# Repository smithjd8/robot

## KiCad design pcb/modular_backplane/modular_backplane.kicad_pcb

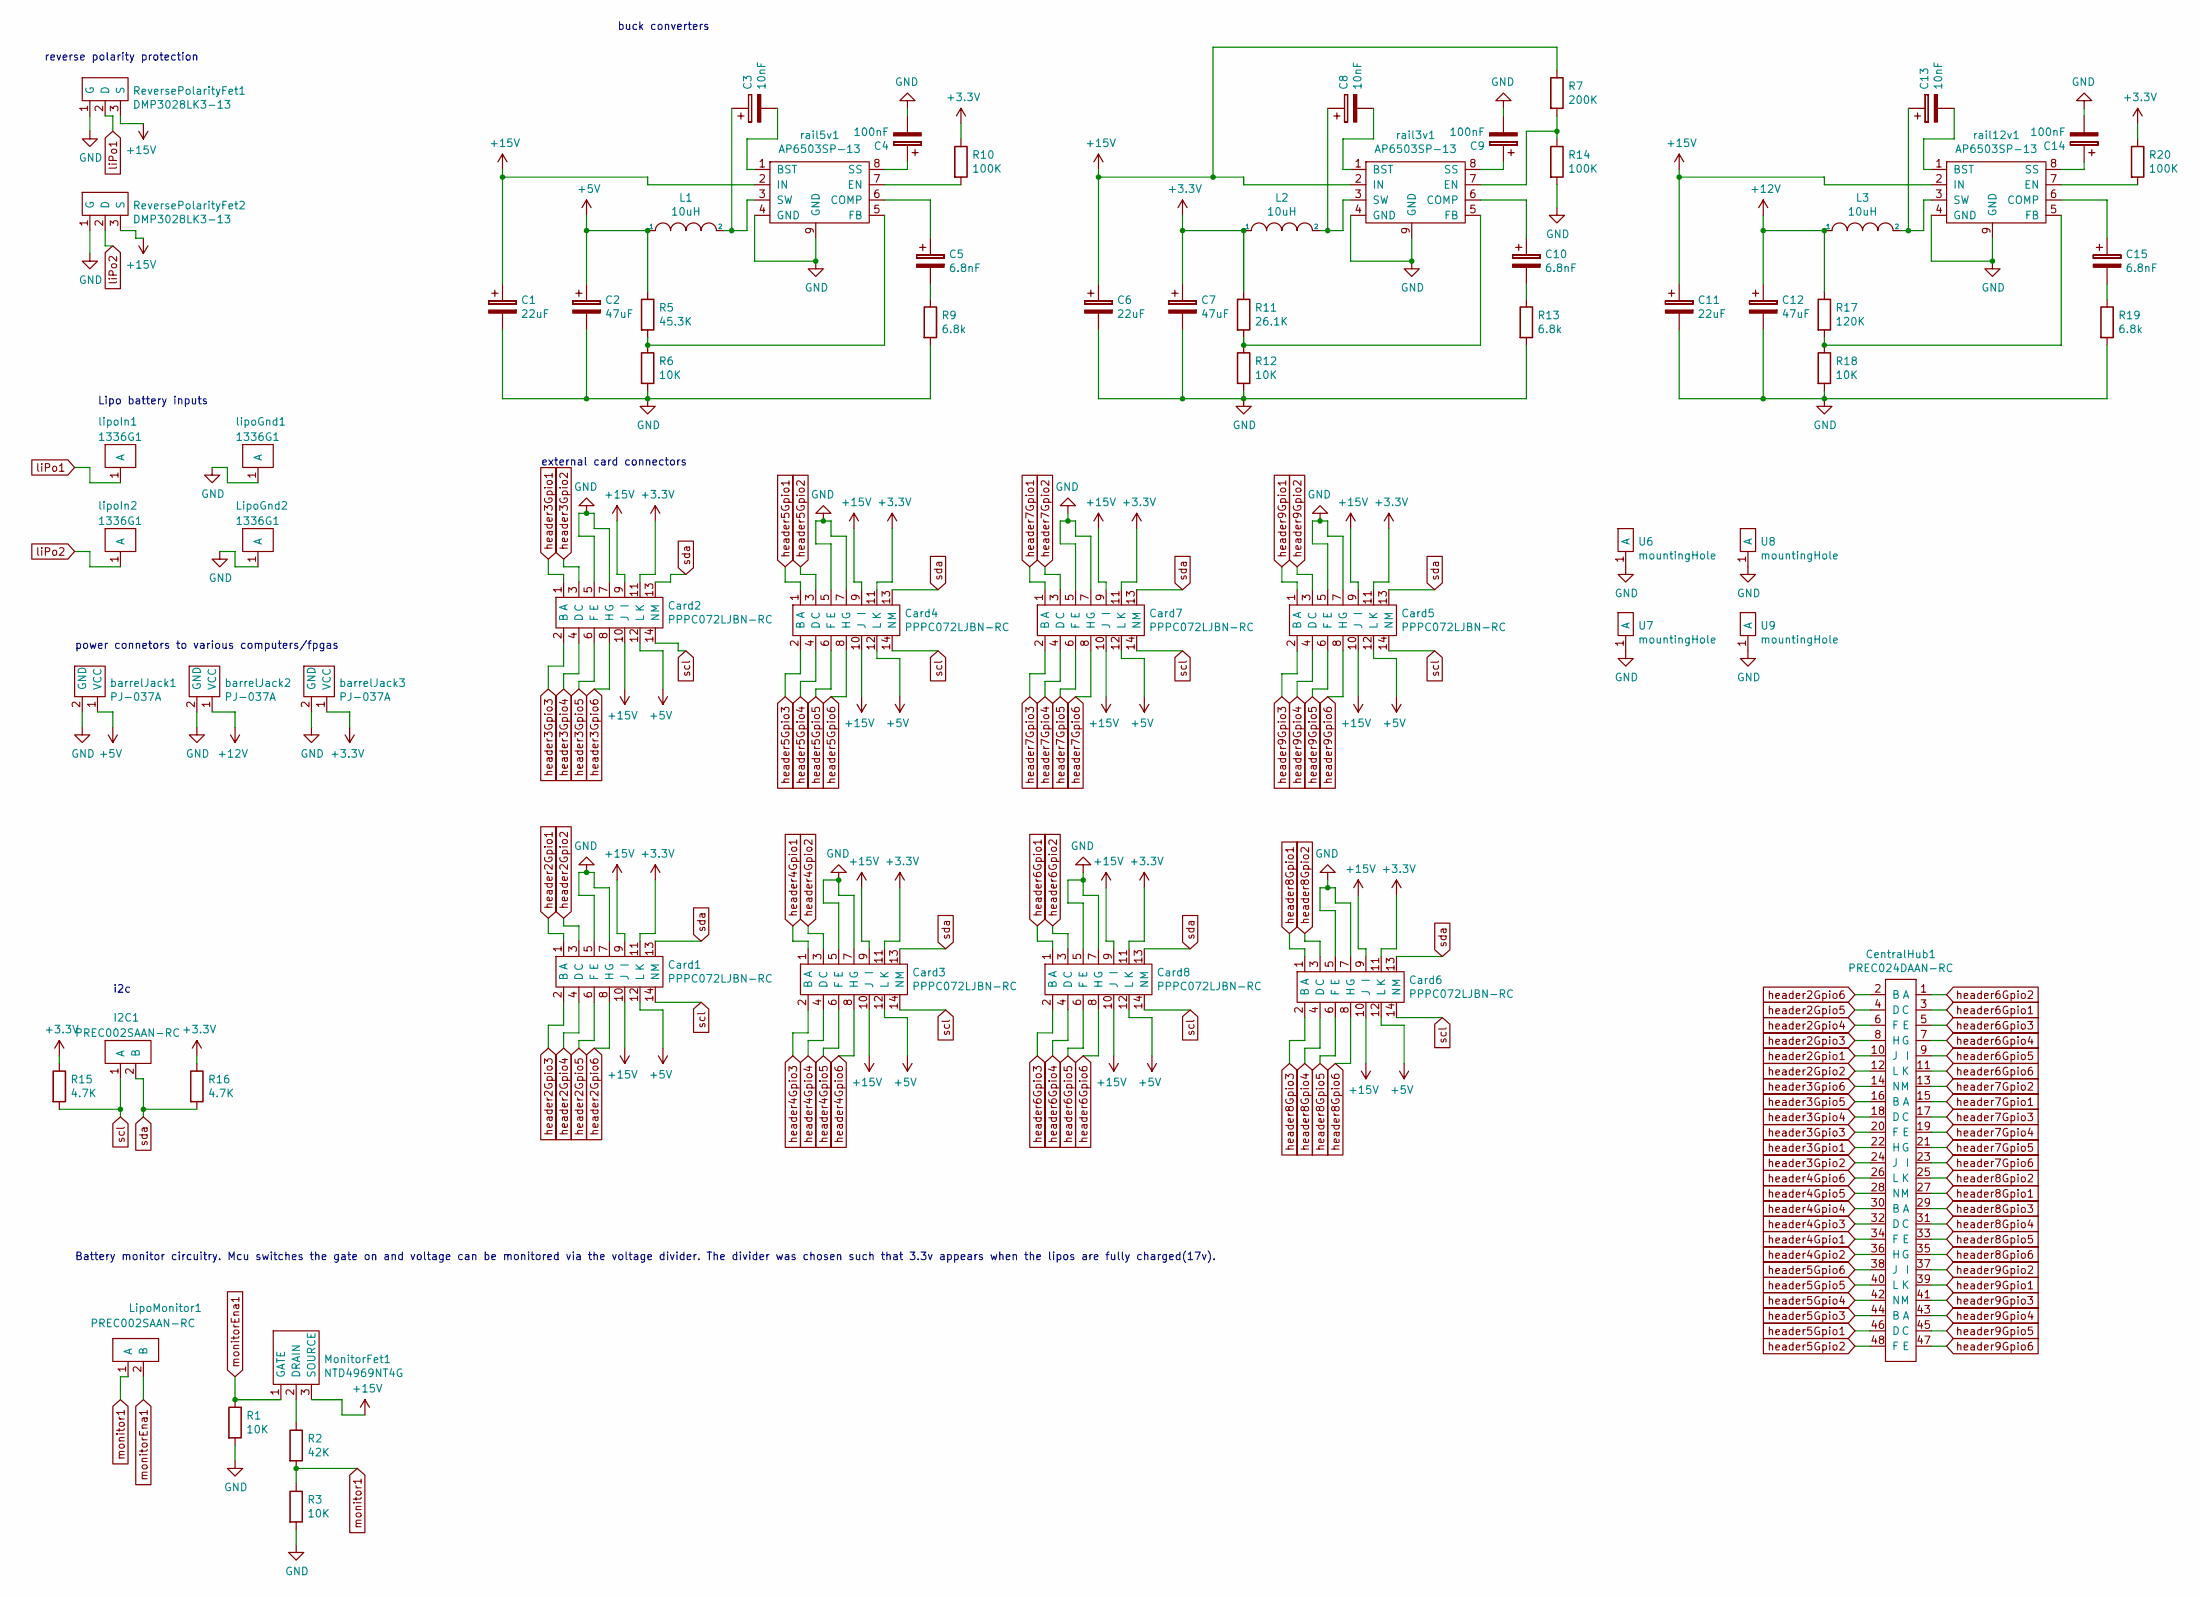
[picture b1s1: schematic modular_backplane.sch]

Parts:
C1, C6, C11: 22uF; 865090442004
C2, C7, C12: 47uF; 865090449007
C3, C8, C13: 10nF; C_1206_3216Metric_Pad1.42x1.75mm_HandSolder
C4, C9, C14: 100nF; C_1206_3216Metric_Pad1.42x1.75mm_HandSolder
C5, C10, C15: 6.8nF; C_1206_3216Metric_Pad1.42x1.75mm_HandSolder
Card1, Card2, Card3, Card4, Card5, Card6, Card7, Card8: PPPC072LJBN-RC
CentralHub1: PREC024DAAN-RC
I2C1: PREC002SAAN-RC
L1, L2, L3: 10uH; RCH8011NP-100L
LipoGnd2: 1336G1
LipoMonitor1: PREC002SAAN-RC
MonitorFet1: NTD4969NT4G
R1, R3, R6, R12, R18: 10K; R_1206_3216Metric_Pad1.42x1.75mm_HandSolder
R2: 42K; R_1206_3216Metric_Pad1.42x1.75mm_HandSolder
R5: 45.3K; R_1206_3216Metric_Pad1.42x1.75mm_HandSolder
R7: 200K; R_1206_3216Metric_Pad1.42x1.75mm_HandSolder
R9, R13, R19: 6.8k; R_1206_3216Metric_Pad1.42x1.75mm_HandSolder
R10, R14, R20: 100K; R_1206_3216Metric_Pad1.42x1.75mm_HandSolder
R11: 26.1K; R_1206_3216Metric_Pad1.42x1.75mm_HandSolder
R15, R16: 4.7K; R_1206_3216Metric_Pad1.42x1.75mm_HandSolder
R17: 120K; R_1206_3216Metric_Pad1.42x1.75mm_HandSolder
ReversePolarityFet1, ReversePolarityFet2: DMP3028LK3-13
U6, U7, U8, U9: mountingHole
barrelJack1, barrelJack2, barrelJack3: PJ-037A
lipoGnd1: 1336G1
lipoIn1, lipoIn2: 1336G1
rail3v1, rail5v1, rail12v1: AP6503SP-13

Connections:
+3V3: C7.1, Card1.11 (K), Card2.11 (K), Card3.11 (K), Card4.11 (K), Card5.11 (K), Card6.11 (K), Card7.11 (K), Card8.11 (K), L2.1, R10.1, R11.1, R15.1, R16.1, R20.1, barrelJack3.1 (VCC)
+5V: C2.1, Card1.12 (L), Card2.12 (L), Card3.12 (L), Card4.12 (L), Card5.12 (L), Card6.12 (L), Card7.12 (L), Card8.12 (L), L1.1, R5.1, barrelJack1.1 (VCC)
+12V: C12.1, L3.1, R17.1, barrelJack2.1 (VCC)
+15V: C1.1, C6.1, C11.1, Card1.9 (I), Card1.10 (J), Card2.9 (I), Card2.10 (J), Card3.9 (I), Card3.10 (J), Card4.9 (I), Card4.10 (J), Card5.9 (I), Card5.10 (J), Card6.9 (I), Card6.10 (J), Card7.9 (I), Card7.10 (J), Card8.9 (I), Card8.10 (J), MonitorFet1.3 (SOURCE), R7.1, ReversePolarityFet1.3 (S), ReversePolarityFet2.3 (S), rail3v1.2 (IN), rail5v1.2 (IN), rail12v1.2 (IN)
GND: C1.2, C2.2, C4.2, C6.2, C7.2, C9.2, C11.2, C12.2, C14.2, Card1.5 (E), Card1.7 (G), Card2.5 (E), Card2.7 (G), Card3.5 (E), Card3.7 (G), Card4.5 (E), Card4.7 (G), Card5.5 (E), Card5.7 (G), Card6.5 (E), Card6.7 (G), Card7.5 (E), Card7.7 (G), Card8.5 (E), Card8.7 (G), LipoGnd2.1, R1.2, R3.2, R6.2, R9.2, R12.2, R13.2, R14.2, R18.2, R19.2, ReversePolarityFet1.1 (G), ReversePolarityFet2.1 (G), U6.1, U7.1, U8.1, U9.1, barrelJack1.2 (GND), barrelJack2.2 (GND), barrelJack3.2 (GND), lipoGnd1.1, rail3v1.4 (GND), rail3v1.9 (GND), rail5v1.4 (GND), rail5v1.9 (GND), rail12v1.4 (GND), rail12v1.9 (GND)
unnamed: C3.1, L1.2, rail5v1.3 (SW)
unnamed: C3.2, rail5v1.1 (BST)
unnamed: C4.1, rail5v1.8 (SS)
unnamed: C5.1, rail5v1.6 (COMP)
unnamed: C5.2, R9.1
unnamed: C8.1, L2.2, rail3v1.3 (SW)
unnamed: C8.2, rail3v1.1 (BST)
unnamed: C9.1, rail3v1.8 (SS)
unnamed: C10.1, rail3v1.6 (COMP)
unnamed: C10.2, R13.1
unnamed: C13.1, L3.2, rail12v1.3 (SW)
unnamed: C13.2, rail12v1.1 (BST)
unnamed: C14.1, rail12v1.8 (SS)
unnamed: C15.1, rail12v1.6 (COMP)
unnamed: C15.2, R19.1
unnamed: MonitorFet1.2 (DRAIN), R2.1
unnamed: R5.2, R6.1, rail5v1.5 (FB)
unnamed: R10.2, rail5v1.7 (EN)
unnamed: R11.2, R12.1, rail3v1.5 (FB)
unnamed: R7.2, R14.1, rail3v1.7 (EN)
unnamed: R17.2, R18.1, rail12v1.5 (FB)
unnamed: R20.2, rail12v1.7 (EN)
header2Gpio1: Card1.1 (A), CentralHub1.10 (J)
header2Gpio2: Card1.3 (C), CentralHub1.12 (L)
header2Gpio3: Card1.2 (B), CentralHub1.8 (H)
header2Gpio4: Card1.4 (D), CentralHub1.6 (F)
header2Gpio5: Card1.6 (F), CentralHub1.4 (D)
header2Gpio6: Card1.8 (H), CentralHub1.2 (B)
header3Gpio1: Card2.1 (A), CentralHub1.22 (H)
header3Gpio2: Card2.3 (C), CentralHub1.24 (J)
header3Gpio3: Card2.2 (B), CentralHub1.20 (F)
header3Gpio4: Card2.4 (D), CentralHub1.18 (D)
header3Gpio5: Card2.6 (F), CentralHub1.16 (B)
header3Gpio6: Card2.8 (H), CentralHub1.14 (N)
header4Gpio1: Card3.1 (A), CentralHub1.34 (F)
header4Gpio2: Card3.3 (C), CentralHub1.36 (H)
header4Gpio3: Card3.2 (B), CentralHub1.32 (D)
header4Gpio4: Card3.4 (D), CentralHub1.30 (B)
header4Gpio5: Card3.6 (F), CentralHub1.28 (N)
header4Gpio6: Card3.8 (H), CentralHub1.26 (L)
header5Gpio1: Card4.1 (A), CentralHub1.46 (D)
header5Gpio2: Card4.3 (C), CentralHub1.48 (F)
header5Gpio3: Card4.2 (B), CentralHub1.44 (B)
header5Gpio4: Card4.4 (D), CentralHub1.42 (N)
header5Gpio5: Card4.6 (F), CentralHub1.40 (L)
header5Gpio6: Card4.8 (H), CentralHub1.38 (J)
header6Gpio1: Card8.1 (A), CentralHub1.3 (C)
header6Gpio2: Card8.3 (C), CentralHub1.1 (A)
header6Gpio3: Card8.2 (B), CentralHub1.5 (E)
header6Gpio4: Card8.4 (D), CentralHub1.7 (G)
header6Gpio5: Card8.6 (F), CentralHub1.9 (I)
header6Gpio6: Card8.8 (H), CentralHub1.11 (K)
header7Gpio1: Card7.1 (A), CentralHub1.15 (A)
header7Gpio2: Card7.3 (C), CentralHub1.13 (M)
header7Gpio3: Card7.2 (B), CentralHub1.17 (C)
header7Gpio4: Card7.4 (D), CentralHub1.19 (E)
header7Gpio5: Card7.6 (F), CentralHub1.21 (G)
header7Gpio6: Card7.8 (H), CentralHub1.23 (I)
header8Gpio1: Card6.1 (A), CentralHub1.27 (M)
header8Gpio2: Card6.3 (C), CentralHub1.25 (K)
header8Gpio3: Card6.2 (B), CentralHub1.29 (A)
header8Gpio4: Card6.4 (D), CentralHub1.31 (C)
header8Gpio5: Card6.6 (F), CentralHub1.33 (E)
header8Gpio6: Card6.8 (H), CentralHub1.35 (G)
header9Gpio1: Card5.1 (A), CentralHub1.39 (K)
header9Gpio2: Card5.3 (C), CentralHub1.37 (I)
header9Gpio3: Card5.2 (B), CentralHub1.41 (M)
header9Gpio4: Card5.4 (D), CentralHub1.43 (A)
header9Gpio5: Card5.6 (F), CentralHub1.45 (C)
header9Gpio6: Card5.8 (H), CentralHub1.47 (E)
liPo1: ReversePolarityFet1.2 (D), lipoIn1.1
liPo2: ReversePolarityFet2.2 (D), lipoIn2.1
monitor1: LipoMonitor1.1 (A), R2.2, R3.1
monitorEna1: LipoMonitor1.2 (B), MonitorFet1.1 (GATE), R1.1
scl: Card1.14 (N), Card2.14 (N), Card3.14 (N), Card4.14 (N), Card5.14 (N), Card6.14 (N), Card7.14 (N), Card8.14 (N), I2C1.1 (A), R15.2
sda: Card1.13 (M), Card2.13 (M), Card3.13 (M), Card4.13 (M), Card5.13 (M), Card6.13 (M), Card7.13 (M), Card8.13 (M), I2C1.2 (B), R16.2

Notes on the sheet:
reverse polarity protection
Lipo battery inputs
power connetors to various computers/fpgas
buck converters
Battery monitor circuitry. Mcu switches the gate on and voltage can be monitored via the voltage divider. The divider was chosen such that 3.3v appears when the lipos are fully charged(17v).
i2c
external card connectors

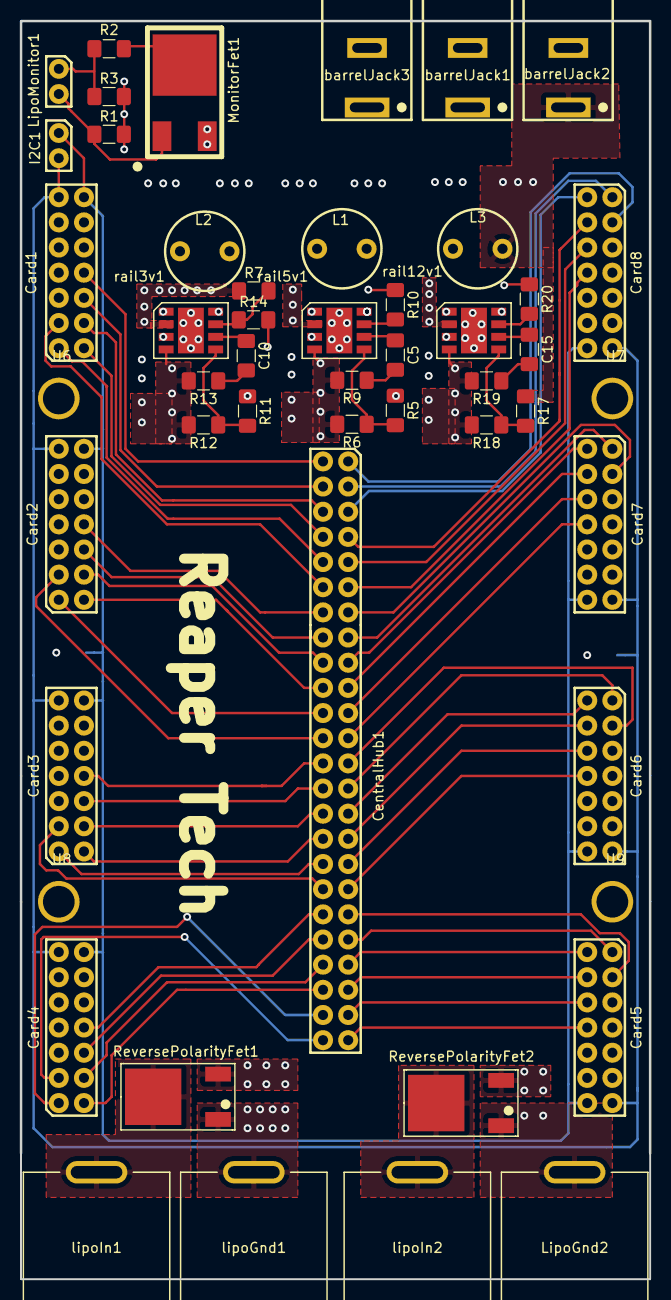
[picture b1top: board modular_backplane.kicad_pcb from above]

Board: 6 copper layers, 63.5 x 127.0 mm, 64 parts (0 on the bottom side), 81 nets.

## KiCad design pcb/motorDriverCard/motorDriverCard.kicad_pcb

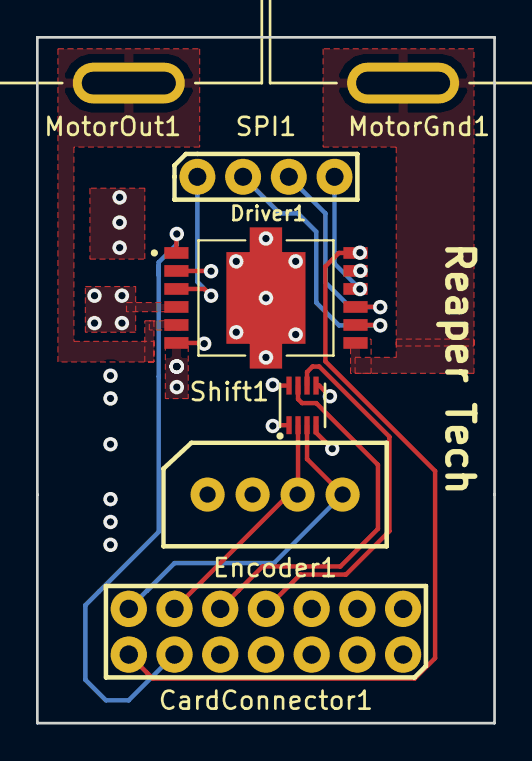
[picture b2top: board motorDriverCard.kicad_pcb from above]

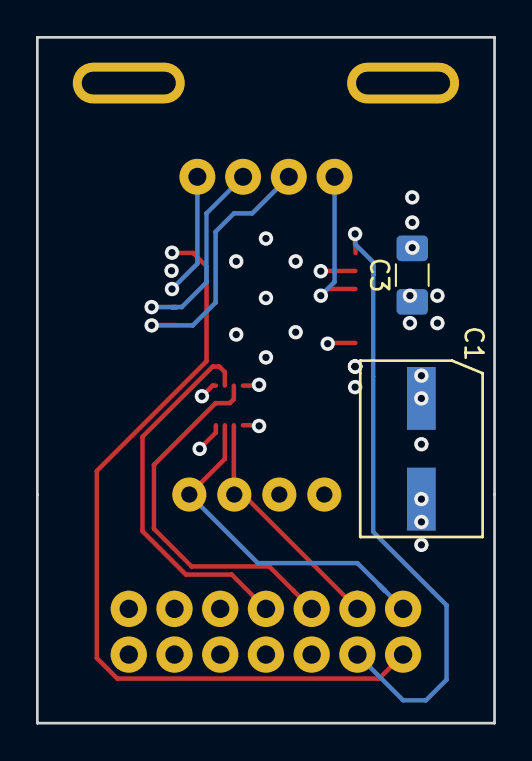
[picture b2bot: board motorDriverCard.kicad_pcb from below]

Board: 6 copper layers, 25.4 x 38.1 mm, 9 parts (2 on the bottom side), 16 nets.

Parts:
C1: 100uF; 865080445010
C3: 100nF; C_1206_3216Metric_Pad1.42x1.75mm_HandSolder
CardConnector1: PEC07DBBN
Driver1: IFX9201SGAUMA1
Encoder1: B4B-XH-A
MotorGnd1: 1336G1
MotorOut1: 1336G1
SPI1: PREC004SAAN-RC
Shift1: 74LVCH2T45DC,125

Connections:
+3V3: CardConnector1.3, Driver1.2, Shift1.5, Shift1.8
+5V: CardConnector1.4, Encoder1.1, Shift1.1
+15V: C1.1, C3.1, CardConnector1.5, CardConnector1.6, Driver1.4
CSN: Driver1.9, SPI1.3
GND: C1.2, C3.2, CardConnector1.7, CardConnector1.9, Driver1.6, Driver1.11, Driver1.13, Encoder1.2, Shift1.4
Motor1EncoderA: CardConnector1.12, Encoder1.3, Shift1.2
Motor1EncoderA_3v3: CardConnector1.10, Shift1.7
Motor1EncoderB: CardConnector1.14, Encoder1.4, Shift1.3
Motor1EncoderB_3v3: CardConnector1.8, Shift1.6
SCK: Driver1.10, SPI1.4
mcuSI: Driver1.8, SPI1.2
mcuSO: Driver1.3, SPI1.1
motorControlOut1: Driver1.5, MotorOut1.1
motorDir1: CardConnector1.11, Driver1.1
motorGnd1: Driver1.7, MotorGnd1.1
motorPwm1: CardConnector1.13, Driver1.12

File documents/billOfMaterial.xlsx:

name | part number | quantity | price | part cost | total cost
powerpole contact | 1336g1 | 12 | 0.62 | 7.4399999999999995
powerpole housing | 1327G6FP-BK | 12 | 0.36 | 4.32
jst | B4B-XH-A | 8 | 0.21 | 1.68
male pin | PREC002SAAN-RC | 12 | 0.06 | 0.72
barrel jack | PJ-037A | 3 | 0.57999999999999996 | 1.7399999999999998
level shifter | 74LVCH2T45DC,125 | 4 | 0.155 | 0.62
PREC004SAAN-RC | male pin | 1 | 0.34 | 0.34
male pin | PREC004SAAN-RC | 5 | 0.12 | 0.6
motor driver | IFX9201SGAUMA1 | 4 | 3.84 | 15.36
regulator | AP6503SP-13 | 3 | 0.94 | 2.82
10K rsistor 1206 | RCG120610K0FKEA | 5 | 0.1 | 0.5
42k resistor 1206 | CRCW120642K2FKEA | 2 | 0.13 | 0.26
6.8k resistor 1206 | CRCW12066K80FKEAC | 3 | 0.19 | 0.57000000000000006
100k resistor 1206 | CRCW1206100KFKEAC | 3 | 0.1 | 0.30000000000000004
p channel mosfet | DMP3028LK3-13 | 2 | 0.56000000000000005 | 1.1200000000000001
inductor 15uH | 6100-150K-RC | 3 | 0.79 | 2.37
10nF | VJ1206Y103JXXPW1BC | 3 | 0.2 | 0.60000000000000009
6.8nF | VJ1206Y682KXXCW1BC | 3 | 0.1 | 0.30000000000000004
47uF | 865090449007 | 3 | 0.48 | 1.44
22uF | 865090442004 | 3 | 0.28000000000000003 | 0.84000000000000008
100nF cap | VJ1206Y104KXXPW1BC | 4 | 0.28999999999999998 | 1.1599999999999999
100uF cap | 865080445010 | 3 | 0.34 | 1.02 | 46.11999999999999

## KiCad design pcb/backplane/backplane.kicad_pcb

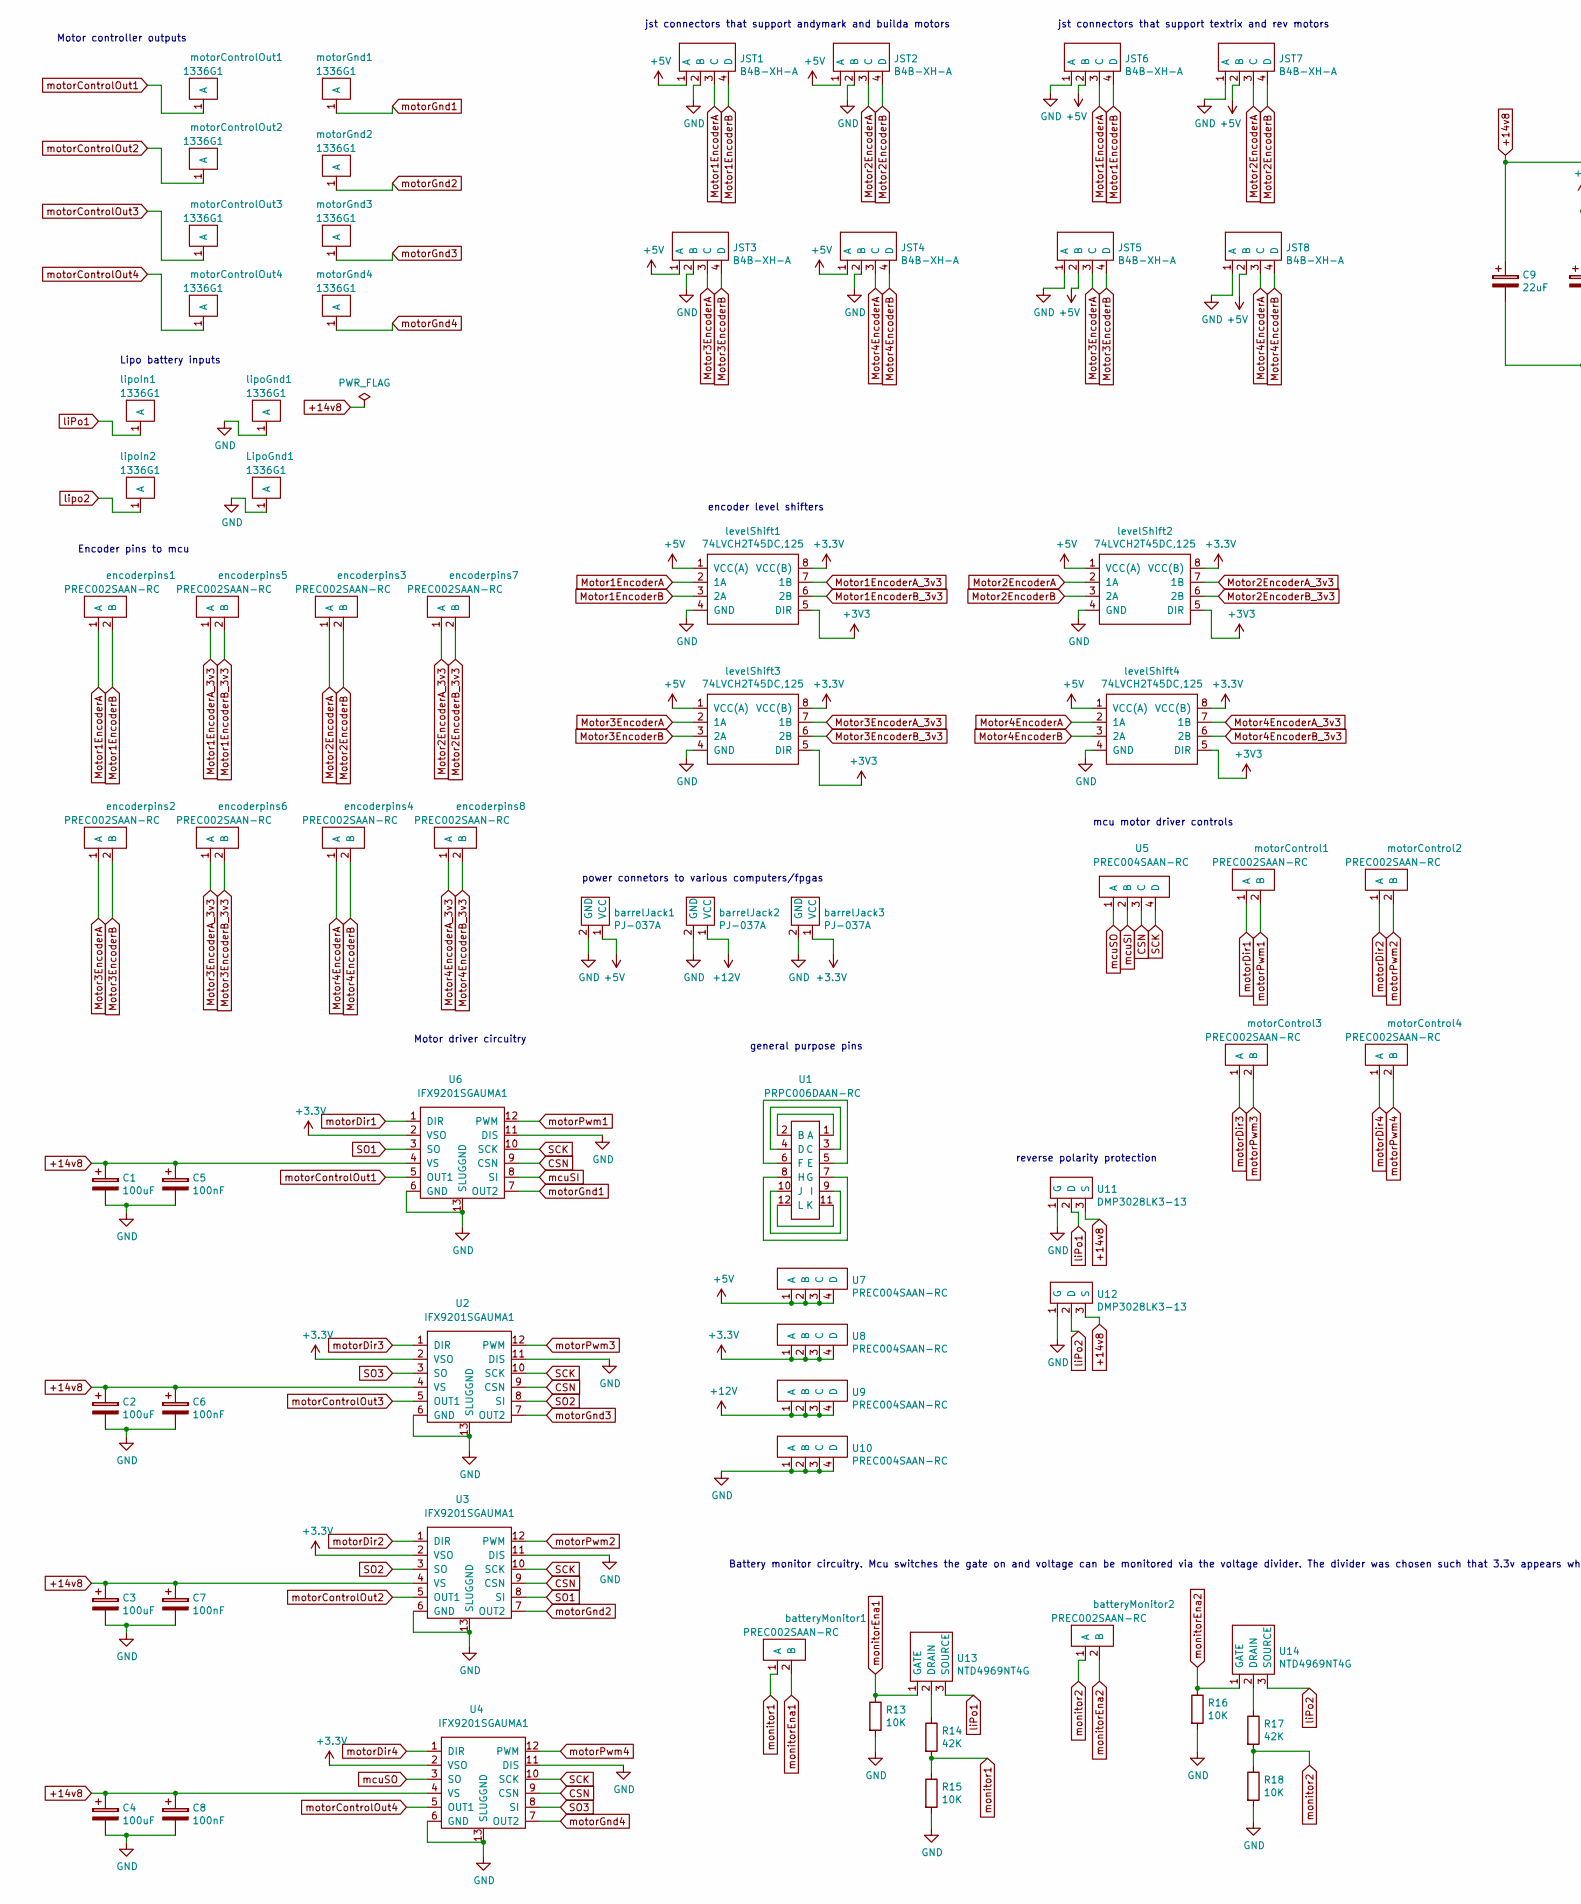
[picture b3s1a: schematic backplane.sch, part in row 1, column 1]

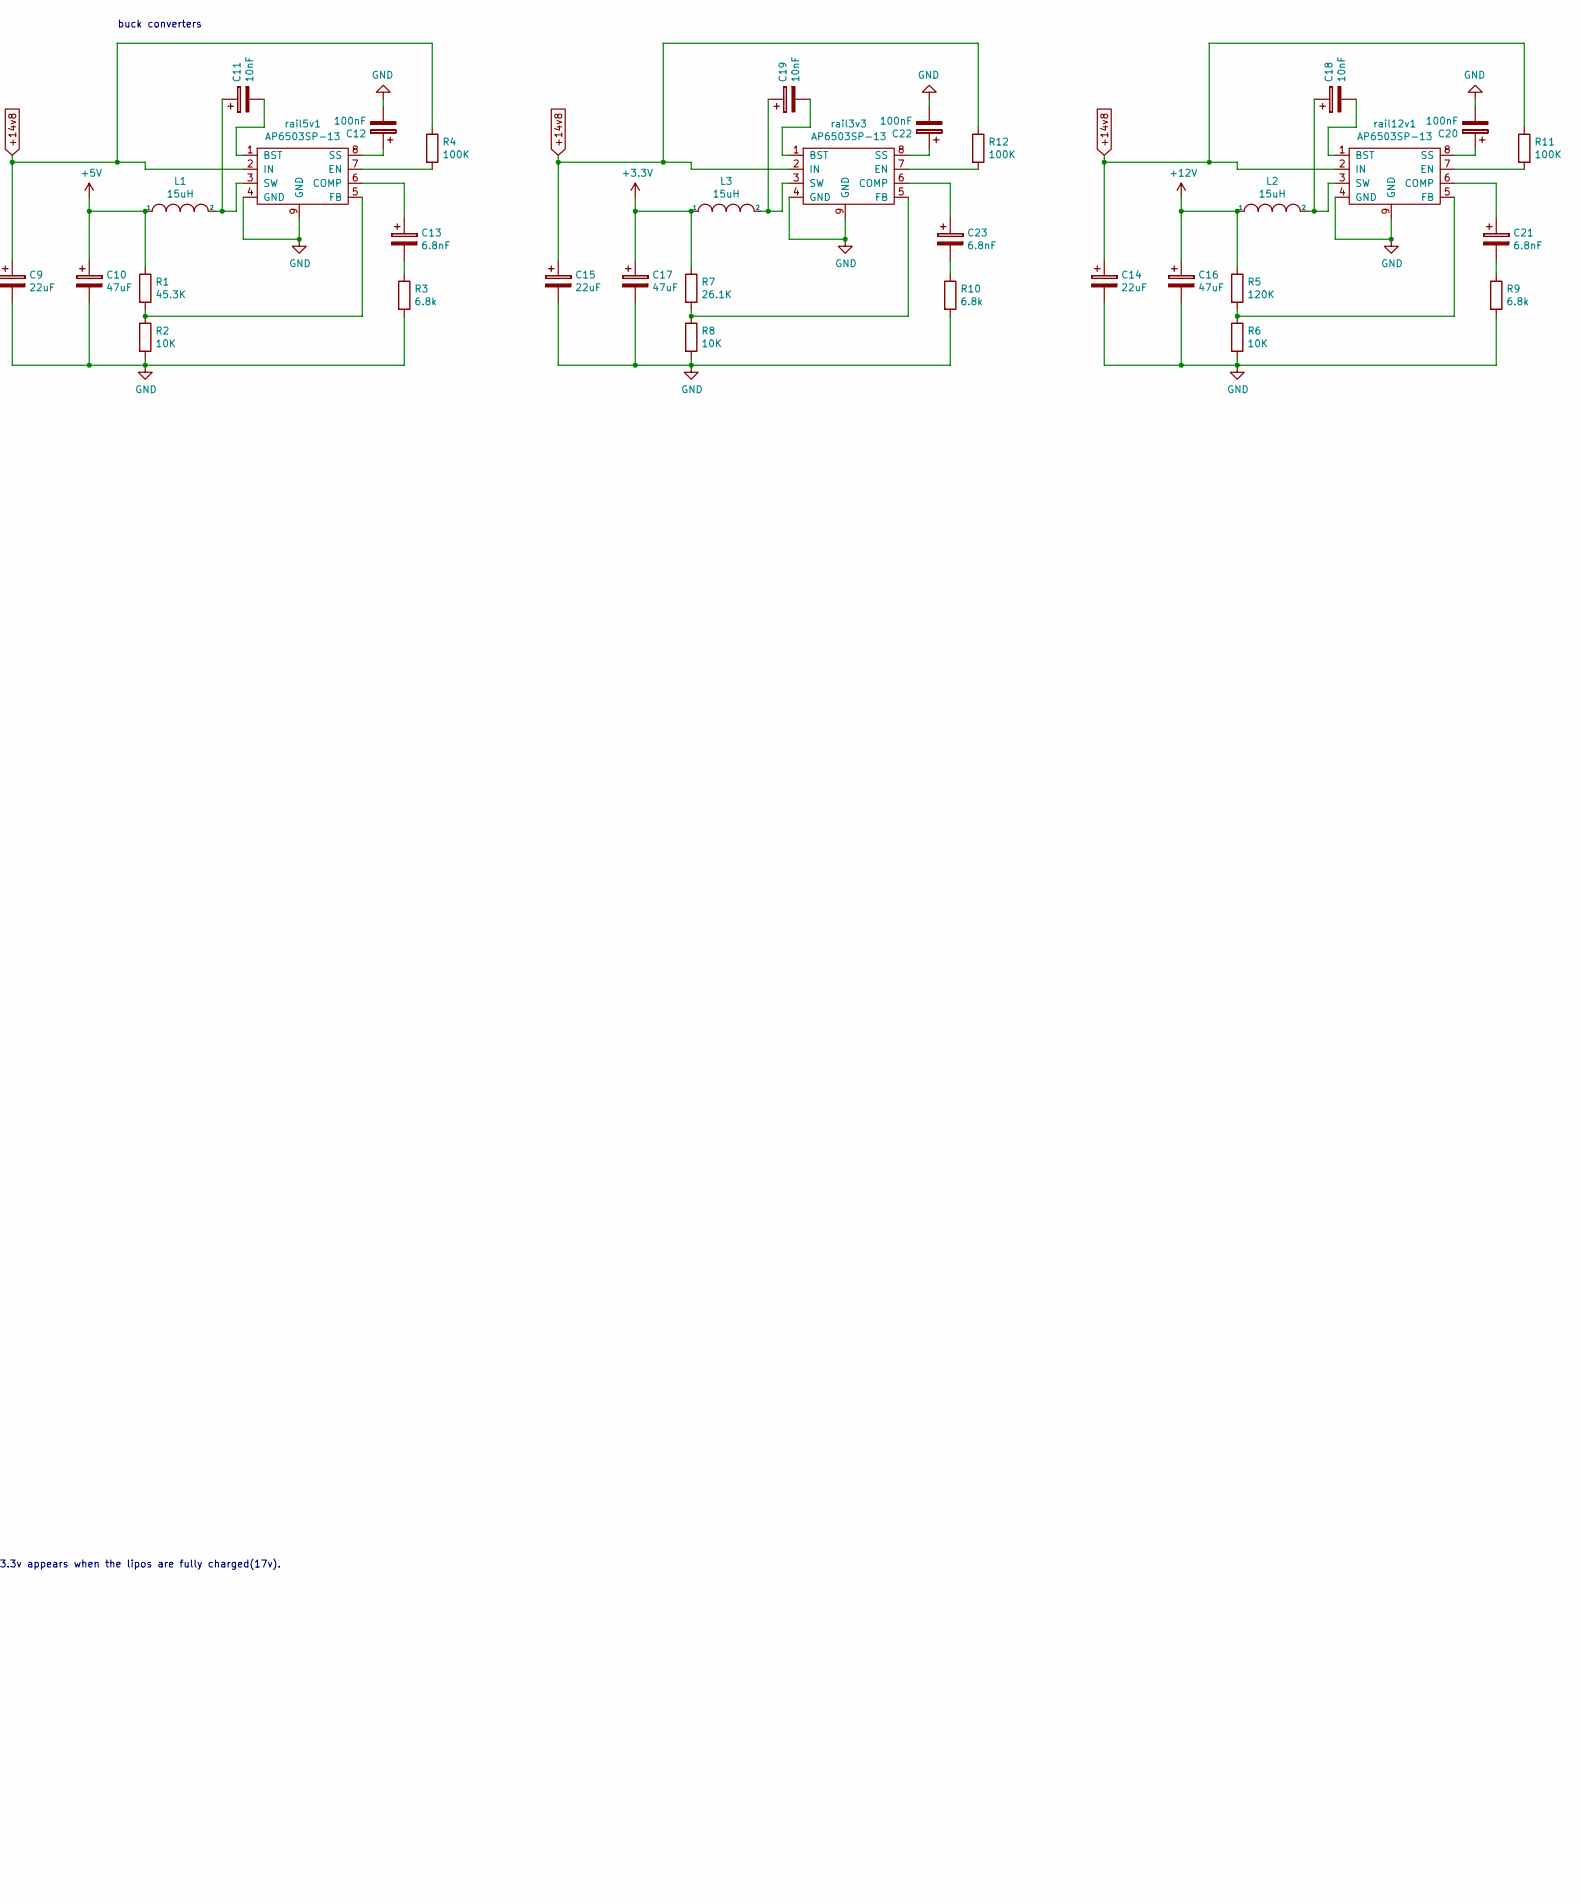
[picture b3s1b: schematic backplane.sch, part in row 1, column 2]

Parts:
C1, C2, C3, C4: 100uF; 865080445010
C5, C6, C7, C8, C12, C20, C22: 100nF; C_1206_3216Metric_Pad1.42x1.75mm_HandSolder
C9, C14, C15: 22uF; 865090442004
C10, C16, C17: 47uF; 865090449007
C11, C18, C19: 10nF; C_1206_3216Metric_Pad1.42x1.75mm_HandSolder
C13, C21, C23: 6.8nF; C_1206_3216Metric_Pad1.42x1.75mm_HandSolder
JST1, JST2, JST3, JST4, JST5, JST6, JST7, JST8: B4B-XH-A
L1, L2, L3: 15uH; 6100-150K-RC
LipoGnd1: 1336G1
R1: 45.3K; R_1206_3216Metric_Pad1.42x1.75mm_HandSolder
R2, R6, R8, R13, R15, R16, R18: 10K; R_1206_3216Metric_Pad1.42x1.75mm_HandSolder
R3, R9, R10: 6.8k; R_1206_3216Metric_Pad1.42x1.75mm_HandSolder
R4, R11, R12: 100K; R_1206_3216Metric_Pad1.42x1.75mm_HandSolder
R5: 120K; R_1206_3216Metric_Pad1.42x1.75mm_HandSolder
R7: 26.1K; R_1206_3216Metric_Pad1.42x1.75mm_HandSolder
R14, R17: 42K; R_1206_3216Metric_Pad1.42x1.75mm_HandSolder
U1: PRPC006DAAN-RC
U2, U3, U4, U6: IFX9201SGAUMA1
U5, U7, U8, U9, U10: PREC004SAAN-RC
U11, U12: DMP3028LK3-13
U13, U14: NTD4969NT4G
barrelJack1, barrelJack2, barrelJack3: PJ-037A
batteryMonitor1, batteryMonitor2: PREC002SAAN-RC
encoderpins1, encoderpins2, encoderpins3, encoderpins4, encoderpins5, encoderpins6, encoderpins7, encoderpins8: PREC002SAAN-RC
levelShift1, levelShift2, levelShift3, levelShift4: 74LVCH2T45DC,125
lipoGnd1: 1336G1
lipoIn1, lipoIn2: 1336G1
motorControl1, motorControl2, motorControl3, motorControl4: PREC002SAAN-RC
motorControlOut1, motorControlOut2, motorControlOut3, motorControlOut4: 1336G1
motorGnd1, motorGnd2, motorGnd3, motorGnd4: 1336G1
rail3v3, rail5v1, rail12v1: AP6503SP-13

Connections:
+5V: C10.1, JST1.1 (A), JST2.1 (A), JST3.1 (A), JST4.1 (A), JST5.2 (B), JST6.2 (B), JST7.2 (B), JST8.2 (B), L1.1, R1.1, U7.1 (A), U7.2 (B), U7.3 (C), U7.4 (D), barrelJack1.1 (VCC), levelShift1.1 (VCC(A)), levelShift2.1 (VCC(A)), levelShift3.1 (VCC(A)), levelShift4.1 (VCC(A))
+12V: C16.1, L2.1, R5.1, U9.1 (A), U9.2 (B), U9.3 (C), U9.4 (D), barrelJack2.1 (VCC)
+14v8: C1.1, C2.1, C3.1, C4.1, C5.1, C6.1, C7.1, C8.1, C9.1, C14.1, C15.1, R4.1, R11.1, R12.1, U2.4 (VS), U3.4 (VS), U4.4 (VS), U6.4 (VS), U11.3 (S), U12.3 (S), rail3v3.2 (IN), rail5v1.2 (IN), rail12v1.2 (IN)
CSN: U2.9 (CSN), U3.9 (CSN), U4.9 (CSN), U5.3 (C), U6.9 (CSN)
GND: C1.2, C2.2, C3.2, C4.2, C5.2, C6.2, C7.2, C8.2, C9.2, C10.2, C12.2, C14.2, C15.2, C16.2, C17.2, C20.2, C22.2, JST1.2 (B), JST2.2 (B), JST3.2 (B), JST4.2 (B), JST5.1 (A), JST6.1 (A), JST7.1 (A), JST8.1 (A), LipoGnd1.1, R2.2, R3.2, R6.2, R8.2, R9.2, R10.2, R13.2, R15.2, R16.2, R18.2, U2.6 (GND), U2.11 (DIS), U2.13 (SLUGGND), U3.6 (GND), U3.11 (DIS), U3.13 (SLUGGND), U4.6 (GND), U4.11 (DIS), U4.13 (SLUGGND), U6.6 (GND), U6.11 (DIS), U6.13 (SLUGGND), U10.1 (A), U10.2 (B), U10.3 (C), U10.4 (D), U11.1 (G), U12.1 (G), barrelJack1.2 (GND), barrelJack2.2 (GND), barrelJack3.2 (GND), levelShift1.4 (GND), levelShift2.4 (GND), levelShift3.4 (GND), levelShift4.4 (GND), lipoGnd1.1, rail3v3.4 (GND), rail3v3.9 (GND), rail5v1.4 (GND), rail5v1.9 (GND), rail12v1.4 (GND), rail12v1.9 (GND)
Motor1EncoderA: JST1.3 (C), JST6.3 (C), encoderpins1.1 (A), levelShift1.2 (1A)
Motor1EncoderA_3v3: encoderpins5.1 (A), levelShift1.7 (1B)
Motor1EncoderB: JST1.4 (D), JST6.4 (D), encoderpins1.2 (B), levelShift1.3 (2A)
Motor1EncoderB_3v3: encoderpins5.2 (B), levelShift1.6 (2B)
Motor2EncoderA: JST2.3 (C), JST7.3 (C), encoderpins3.1 (A), levelShift2.2 (1A)
Motor2EncoderA_3v3: encoderpins7.1 (A), levelShift2.7 (1B)
Motor2EncoderB: JST2.4 (D), JST7.4 (D), encoderpins3.2 (B), levelShift2.3 (2A)
Motor2EncoderB_3v3: encoderpins7.2 (B), levelShift2.6 (2B)
Motor3EncoderA: JST3.3 (C), JST5.3 (C), encoderpins2.1 (A), levelShift3.2 (1A)
Motor3EncoderA_3v3: encoderpins6.1 (A), levelShift3.7 (1B)
Motor3EncoderB: JST3.4 (D), JST5.4 (D), encoderpins2.2 (B), levelShift3.3 (2A)
Motor3EncoderB_3v3: encoderpins6.2 (B), levelShift3.6 (2B)
Motor4EncoderA: JST4.3 (C), JST8.3 (C), encoderpins4.1 (A), levelShift4.2 (1A)
Motor4EncoderA_3v3: encoderpins8.1 (A), levelShift4.7 (1B)
Motor4EncoderB: JST4.4 (D), JST8.4 (D), encoderpins4.2 (B), levelShift4.3 (2A)
Motor4EncoderB_3v3: encoderpins8.2 (B), levelShift4.6 (2B)
unnamed: C11.1, L1.2, rail5v1.3 (SW)
unnamed: C11.2, rail5v1.1 (BST)
unnamed: C12.1, rail5v1.8 (SS)
unnamed: C13.1, rail5v1.6 (COMP)
unnamed: C13.2, R3.1
unnamed: C18.1, L2.2, rail12v1.3 (SW)
unnamed: C18.2, rail12v1.1 (BST)
unnamed: C19.1, L3.2, rail3v3.3 (SW)
unnamed: C19.2, rail3v3.1 (BST)
unnamed: C20.1, rail12v1.8 (SS)
unnamed: C21.1, rail12v1.6 (COMP)
unnamed: C21.2, R9.1
unnamed: C22.1, rail3v3.8 (SS)
unnamed: C23.1, rail3v3.6 (COMP)
unnamed: C23.2, R10.1
unnamed: R1.2, R2.1, rail5v1.5 (FB)
unnamed: R4.2, rail5v1.7 (EN)
unnamed: R5.2, R6.1, rail12v1.5 (FB)
unnamed: R7.2, R8.1, rail3v3.5 (FB)
unnamed: R11.2, rail12v1.7 (EN)
unnamed: R12.2, rail3v3.7 (EN)
unnamed: R14.1, U13.2 (DRAIN)
unnamed: R17.1, U14.2 (DRAIN)
unnamed: U1.1 (A), U1.2 (B)
unnamed: U1.3 (C), U1.4 (D)
unnamed: U1.5 (E), U1.6 (F)
unnamed: U1.7 (G), U1.8 (H)
unnamed: U1.9 (I), U1.10 (J)
unnamed: U1.11 (K), U1.12 (L)
SCK: U2.10 (SCK), U3.10 (SCK), U4.10 (SCK), U5.4 (D), U6.10 (SCK)
SO1: U3.8 (SI), U6.3 (SO)
SO2: U2.8 (SI), U3.3 (SO)
SO3: U2.3 (SO), U4.8 (SI)
liPo1: U11.2 (D), U13.3 (SOURCE), lipoIn1.1
liPo2: U12.2 (D), U14.3 (SOURCE)
lipo2: lipoIn2.1
mcuSI: U5.2 (B), U6.8 (SI)
mcuSO: U4.3 (SO), U5.1 (A)
monitor1: R14.2, R15.1, batteryMonitor1.1 (A)
monitor2: R17.2, R18.1, batteryMonitor2.1 (A)
monitorEna1: R13.1, U13.1 (GATE), batteryMonitor1.2 (B)
monitorEna2: R16.1, U14.1 (GATE), batteryMonitor2.2 (B)
motorControlOut1: U6.5 (OUT1), motorControlOut1.1
motorControlOut2: U3.5 (OUT1), motorControlOut2.1
motorControlOut3: U2.5 (OUT1), motorControlOut3.1
motorControlOut4: U4.5 (OUT1), motorControlOut4.1
motorDir1: U6.1 (DIR), motorControl1.1 (A)
motorDir2: U3.1 (DIR), motorControl2.1 (A)
motorDir3: U2.1 (DIR), motorControl3.1 (A)
motorDir4: U4.1 (DIR), motorControl4.1 (A)
motorGnd1: U6.7 (OUT2), motorGnd1.1
motorGnd2: U3.7 (OUT2), motorGnd2.1
motorGnd3: U2.7 (OUT2), motorGnd3.1
motorGnd4: U4.7 (OUT2), motorGnd4.1
motorPwm1: U6.12 (PWM), motorControl1.2 (B)
motorPwm2: U3.12 (PWM), motorControl2.2 (B)
motorPwm3: U2.12 (PWM), motorControl3.2 (B)
motorPwm4: U4.12 (PWM), motorControl4.2 (B)

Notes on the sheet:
jst connectors that support andymark and builda motors
jst connectors that support textrix and rev motors
Battery monitor circuitry. Mcu switches the gate on and voltage can be monitored via the voltage divider. The divider was chosen such that 3.3v appears when the lipos are fully charged(17v).
Motor driver circuitry
general purpose pins
reverse polarity protection
Encoder pins to mcu
Lipo battery inputs
Motor controller outputs
power connetors to various computers/fpgas
mcu motor driver controls
encoder level shifters
buck converters

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
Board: 2 copper layers, 102 parts (0 on the bottom side), 79 nets, no tracks yet.

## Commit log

2019-01-05 initial matlab code
2019-01-05 initial documents
2019-01-05 pcb start
    started a pcb design
2019-01-06 footprints
    added footprints
2019-01-07 updated pcb
    added footprints and schematic
2019-01-10 updated footprints
2019-01-13 updates
    finished choosing parts and completed the schematic
2019-01-15 changed to a modular design
2019-01-17 layers
    i added plane layers to prepare for routing
2019-01-18 added 12v line
2019-01-20 done
2019-01-20 motordriver finished
2019-01-24 voltage divider
